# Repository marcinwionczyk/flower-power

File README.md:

# flower-power
This is a firmware code for flower watering station which can water up to 3 flowers.

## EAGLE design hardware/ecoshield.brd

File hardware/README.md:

# flower-power
Hardware was designed with Autodesk Eagle

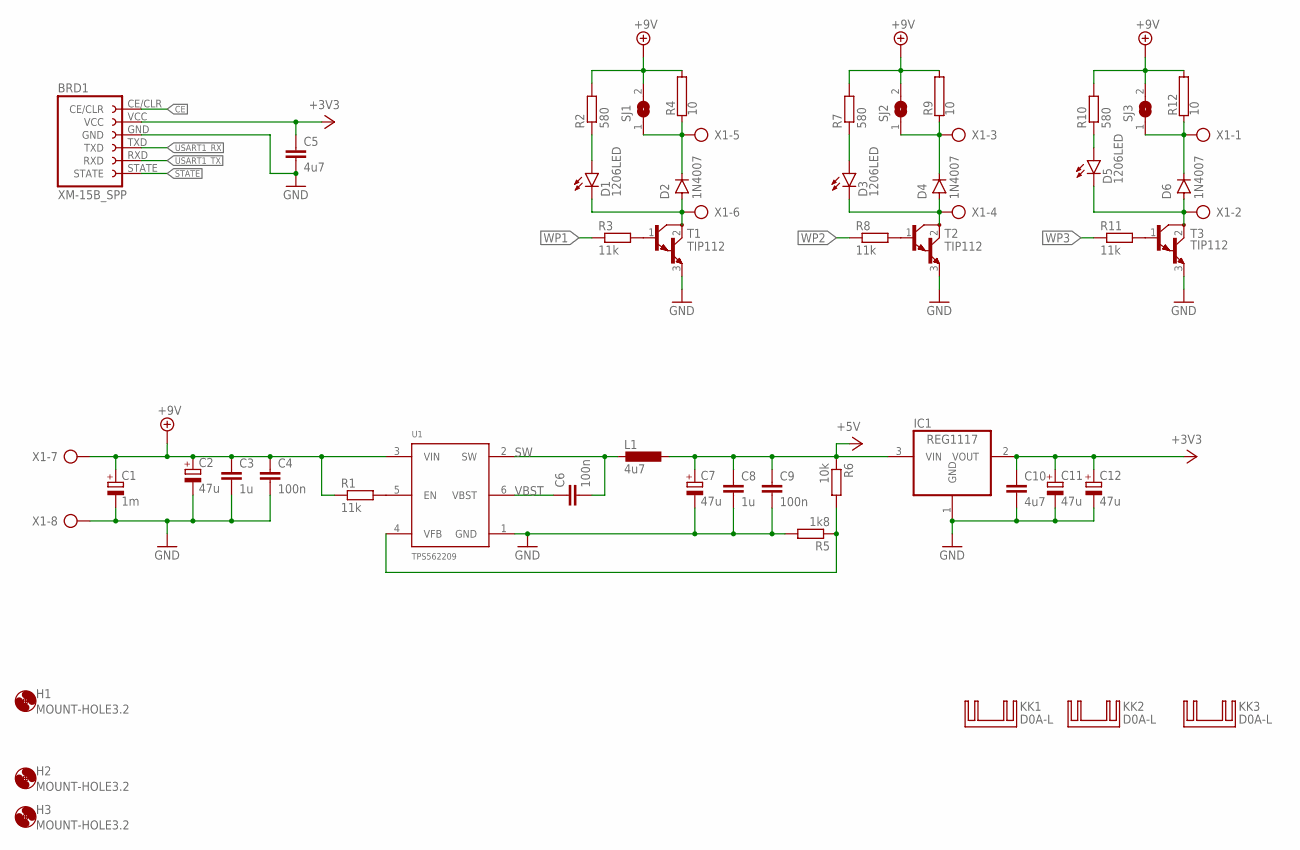
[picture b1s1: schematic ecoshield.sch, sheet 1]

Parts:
BRD1: XM-15B_SPP; XM-15BSPP
C1: 1m; E5-10,5
C2, C7, C11, C12: 47u; SMC_C
C3, C8: 1u; C0805
C4, C6, C9: 100n; C0805
C5, C10: 4u7; C0805
D1, D3, D5: 1206LED; DIOC3216X70N
D2, D4, D6: 1N4007; DIOMELF4925N
H1, H2, H3: MOUNT-HOLE3.2; 3,2
IC1: REG1117; SOT223
KK1, KK2, KK3: D0A-L; D02A-L
L1: 4u7; 744043004.
R1, R3, R8, R11: 11k; R1206
R2, R7, R10: 580; R1206
R4, R9, R12: 10; AC05
R5: 1k8; R1206
R6: 10k; R1206
SJ1, SJ2, SJ3: SJW
T1, T2, T3: TIP112; TO220
U1: TPS562209; SOT95P280X110-6N
X1: AK500/8

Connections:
+3V3: BRD1.VCC, C5.1, C10.1, C11.+, C12.+, IC1.2 (VOUT); also elsewhere on the board
+5V: C7.+, C8.1, C9.1, IC1.3 (VIN), L1.P$1 (1), R6.1
+9V: C1.+, C2.+, C3.1, C4.1, R1.1, R2.2, R4.2, R7.2, R9.2, R10.2, R12.2, SJ1.2, SJ2.2, SJ3.2, U1.3 (VIN), X1.7
CE: BRD1.CE/CLR; also elsewhere on the board
GND: BRD1.GND, C1.-, C2.-, C3.2, C4.2, C5.2, C7.-, C8.2, C9.2, C10.2, C11.-, C12.-, IC1.1 (GND), R5.2, T1.3 (E), T2.3 (E), T3.3 (E), U1.1 (GND), X1.8; also elsewhere on the board
unnamed: R11.2, T3.1 (B)
unnamed: D3.1 (C), D4.2 (A), T2.2 (C), X1.4
unnamed: D4.1 (C), R9.1, SJ2.1, X1.3
unnamed: R8.2, T2.1 (B)
unnamed: R1.2, U1.5 (EN)
unnamed: D6.1 (C), R12.1, SJ3.1, X1.1
unnamed: D3.2 (A), R7.1
unnamed: D5.2 (A), R10.1
unnamed: D5.1 (C), D6.2 (A), T3.2 (C), X1.2
unnamed: D1.1 (C), D2.2 (A), T1.2 (C), X1.6
unnamed: D2.1 (C), R4.1, SJ1.1, X1.5
unnamed: R3.2, T1.1 (B)
unnamed: D1.2 (A), R2.1
unnamed: R5.1, R6.2, U1.4 (VFB)
STATE: BRD1.STATE; also elsewhere on the board
SW: C6.2, L1.P$2 (2), U1.2 (SW)
USART1_RX: BRD1.TXD; also elsewhere on the board
USART1_TX: BRD1.RXD; also elsewhere on the board
VBST: C6.1, U1.6 (VBST)
WP1: R3.1; also elsewhere on the board
WP2: R8.1; also elsewhere on the board
WP3: R11.1; also elsewhere on the board

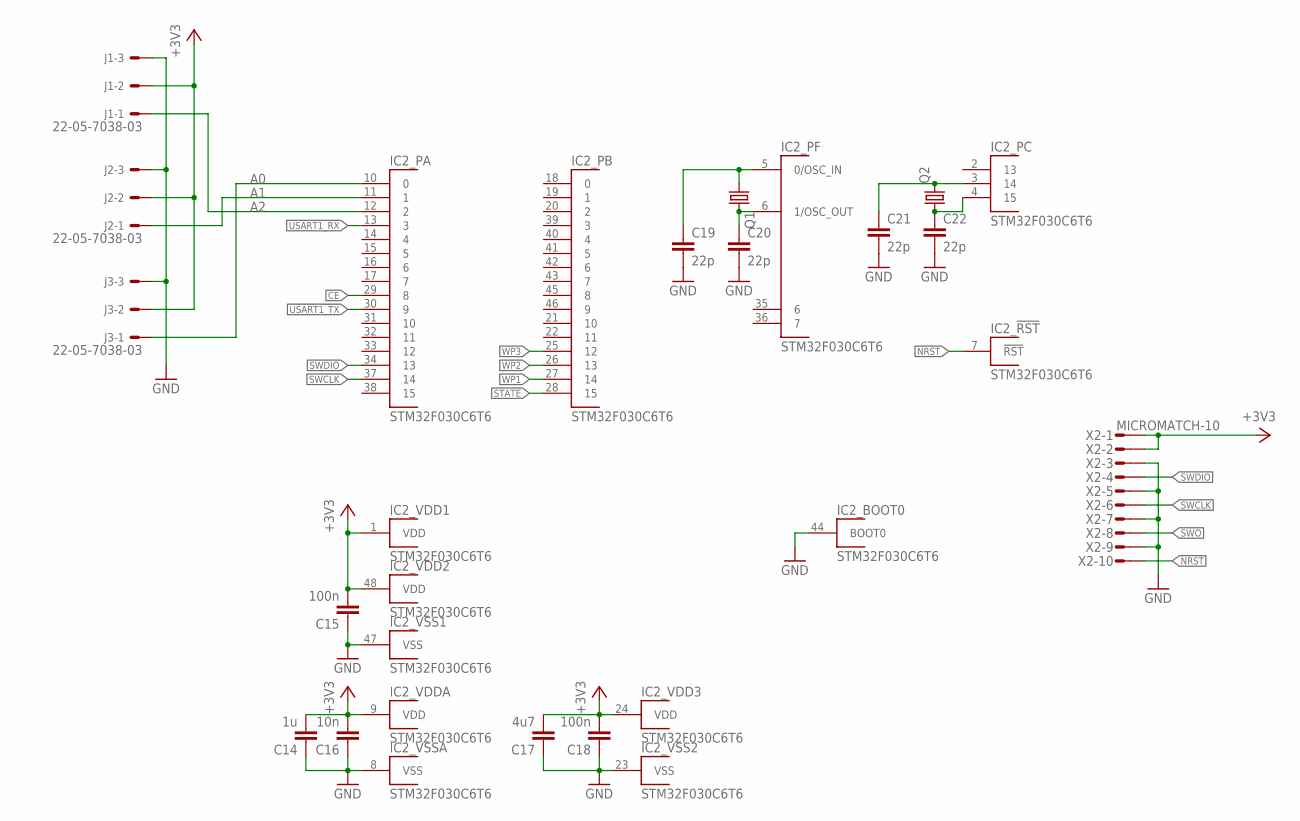
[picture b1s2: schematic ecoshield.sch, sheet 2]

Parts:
C14: 1u; C0805
C15, C18: 100n; C0805
C16: 10n; C0805
C17: 4u7; C0805
C19, C20, C21, C22: 22p; C0603
IC2: STM32F030C6T6; QFP50P900X900X160-48N
J1, J2, J3: 22-05-7038-03; 7395-03
Q1: CRYSTALHC49U-V; HC49U-V
Q2: CRYSTALTC38H; TC38H
X2: MICROMATCH-10

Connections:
+3V3: C14.2, C15.2, C16.2, C17.2, C18.2, IC2.1 (VDD), IC2.9 (VDD), IC2.24 (VDD), IC2.48 (VDD), J1.2, J2.2, J3.2, X2.1, X2.2; also elsewhere on the board
A0: IC2.10 (0), J3.1
A1: IC2.11 (1), J2.1
A2: IC2.12 (2), J1.1
CE: IC2.29 (8); also elsewhere on the board
GND: C14.1, C15.1, C16.1, C17.1, C18.1, C19.2, C20.2, C21.2, C22.2, IC2.8 (VSS), IC2.23 (VSS), IC2.44 (BOOT0), IC2.47 (VSS), J1.3, J2.3, J3.3, X2.3, X2.5, X2.7, X2.9; also elsewhere on the board
unnamed: C20.1, IC2.6 (1/OSC_OUT), Q1.2
unnamed: C19.1, IC2.5 (0/OSC_IN), Q1.1
unnamed: C22.1, IC2.4 (15), Q2.1
unnamed: C21.1, IC2.3 (14), Q2.2
NRST: IC2.7 (!RST), X2.10
STATE: IC2.28 (15); also elsewhere on the board
SWCLK: IC2.37 (14), X2.6
SWDIO: IC2.34 (13), X2.4
SWO: X2.8
USART1_RX: IC2.13 (3); also elsewhere on the board
USART1_TX: IC2.30 (9); also elsewhere on the board
WP1: IC2.27 (14); also elsewhere on the board
WP2: IC2.26 (13); also elsewhere on the board
WP3: IC2.25 (12); also elsewhere on the board

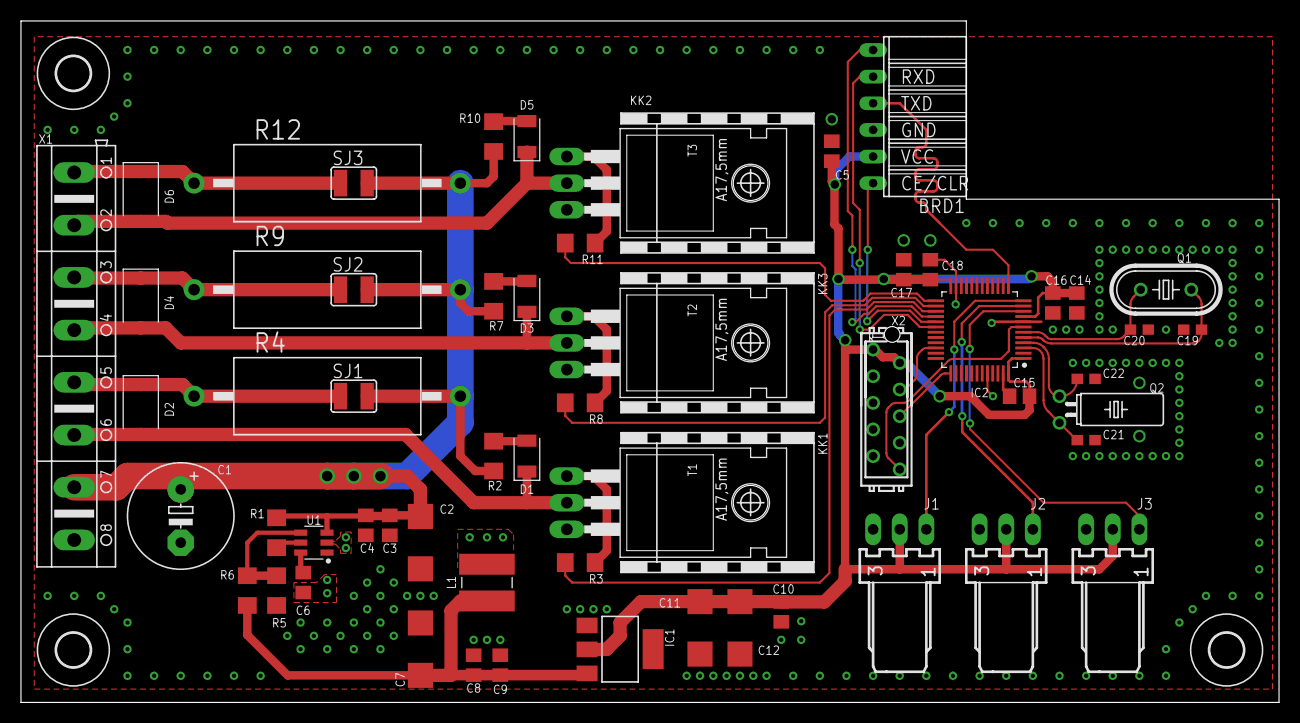
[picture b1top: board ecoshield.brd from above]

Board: 2 copper layers, 120.0 x 65.0 mm, 63 parts (0 on the bottom side), 37 nets.

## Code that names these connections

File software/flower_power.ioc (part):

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Mcu.Name=STM32F030C6Tx
Mcu.Package=LQFP48
Mcu.UserName=STM32F030C6Tx
PA0.GPIOParameters=GPIO_Label
PA0.GPIO_Label=A0
PA0.Mode=IN0
PA0.Signal=ADC_IN0
PA1.GPIOParameters=GPIO_Label
PA1.GPIO_Label=A1
PA1.Mode=IN1
PA1.Signal=ADC_IN1
PA13.Mode=Serial_Wire
PA13.Signal=SYS_SWDIO
PA14.Mode=Serial_Wire
PA14.Signal=SYS_SWCLK
PA2.GPIOParameters=GPIO_Label
PA2.GPIO_Label=A2
PA2.Mode=IN2
PA2.Signal=ADC_IN2
PA3.Mode=Asynchronous
PA3.Signal=USART1_RX
PA8.GPIOParameters=GPIO_Label
PA8.GPIO_Label=CE
PA8.Signal=GPIO_Output
PA9.Mode=Asynchronous
PA9.Signal=USART1_TX
PB12.GPIOParameters=GPIO_Label
PB12.GPIO_Label=WP3
PB12.Signal=GPIO_Output
PB13.GPIOParameters=GPIO_Label
PB13.GPIO_Label=WP2
PB13.Signal=GPIO_Output
PB14.GPIOParameters=GPIO_Label
PB14.GPIO_Label=WP1
PB14.Signal=GPIO_Output
PB15.GPIOParameters=GPIO_Label
PB15.GPIO_Label=STATE
PB15.Signal=GPIO_Input
PC14-OSC32_IN.Mode=LSE-External-Oscillator
PC14-OSC32_IN.Signal=RCC_OSC32_IN
PC15-OSC32_OUT.Mode=LSE-External-Oscillator
PC15-OSC32_OUT.Signal=RCC_OSC32_OUT
PF0-OSC_IN.Mode=HSE-External-Oscillator
PF0-OSC_IN.Signal=RCC_OSC_IN
PF1-OSC_OUT.Mode=HSE-External-Oscillator
PF1-OSC_OUT.Signal=RCC_OSC_OUT
RCC.HSE_VALUE=16000000
RCC.SYSCLKFreq_VALUE=48000000
RCC.SYSCLKSource=RCC_SYSCLKSOURCE_PLLCLK
board=custom

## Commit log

2022-06-16 initial commit. Testing is required.
2022-06-16 this stuff should be deleted
2022-07-03 Remade software with Rust and cortex-m-template (because why not)
2022-07-03 fixed README.md
2022-07-03 added hardware
2022-07-03 replaced schematics.pdf (now it has all pages)
